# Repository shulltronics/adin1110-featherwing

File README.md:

ADIN1110 Single Pair Ethernet FeatherWing
=========================================

### By Carsten Thue-Bludworth, 2023

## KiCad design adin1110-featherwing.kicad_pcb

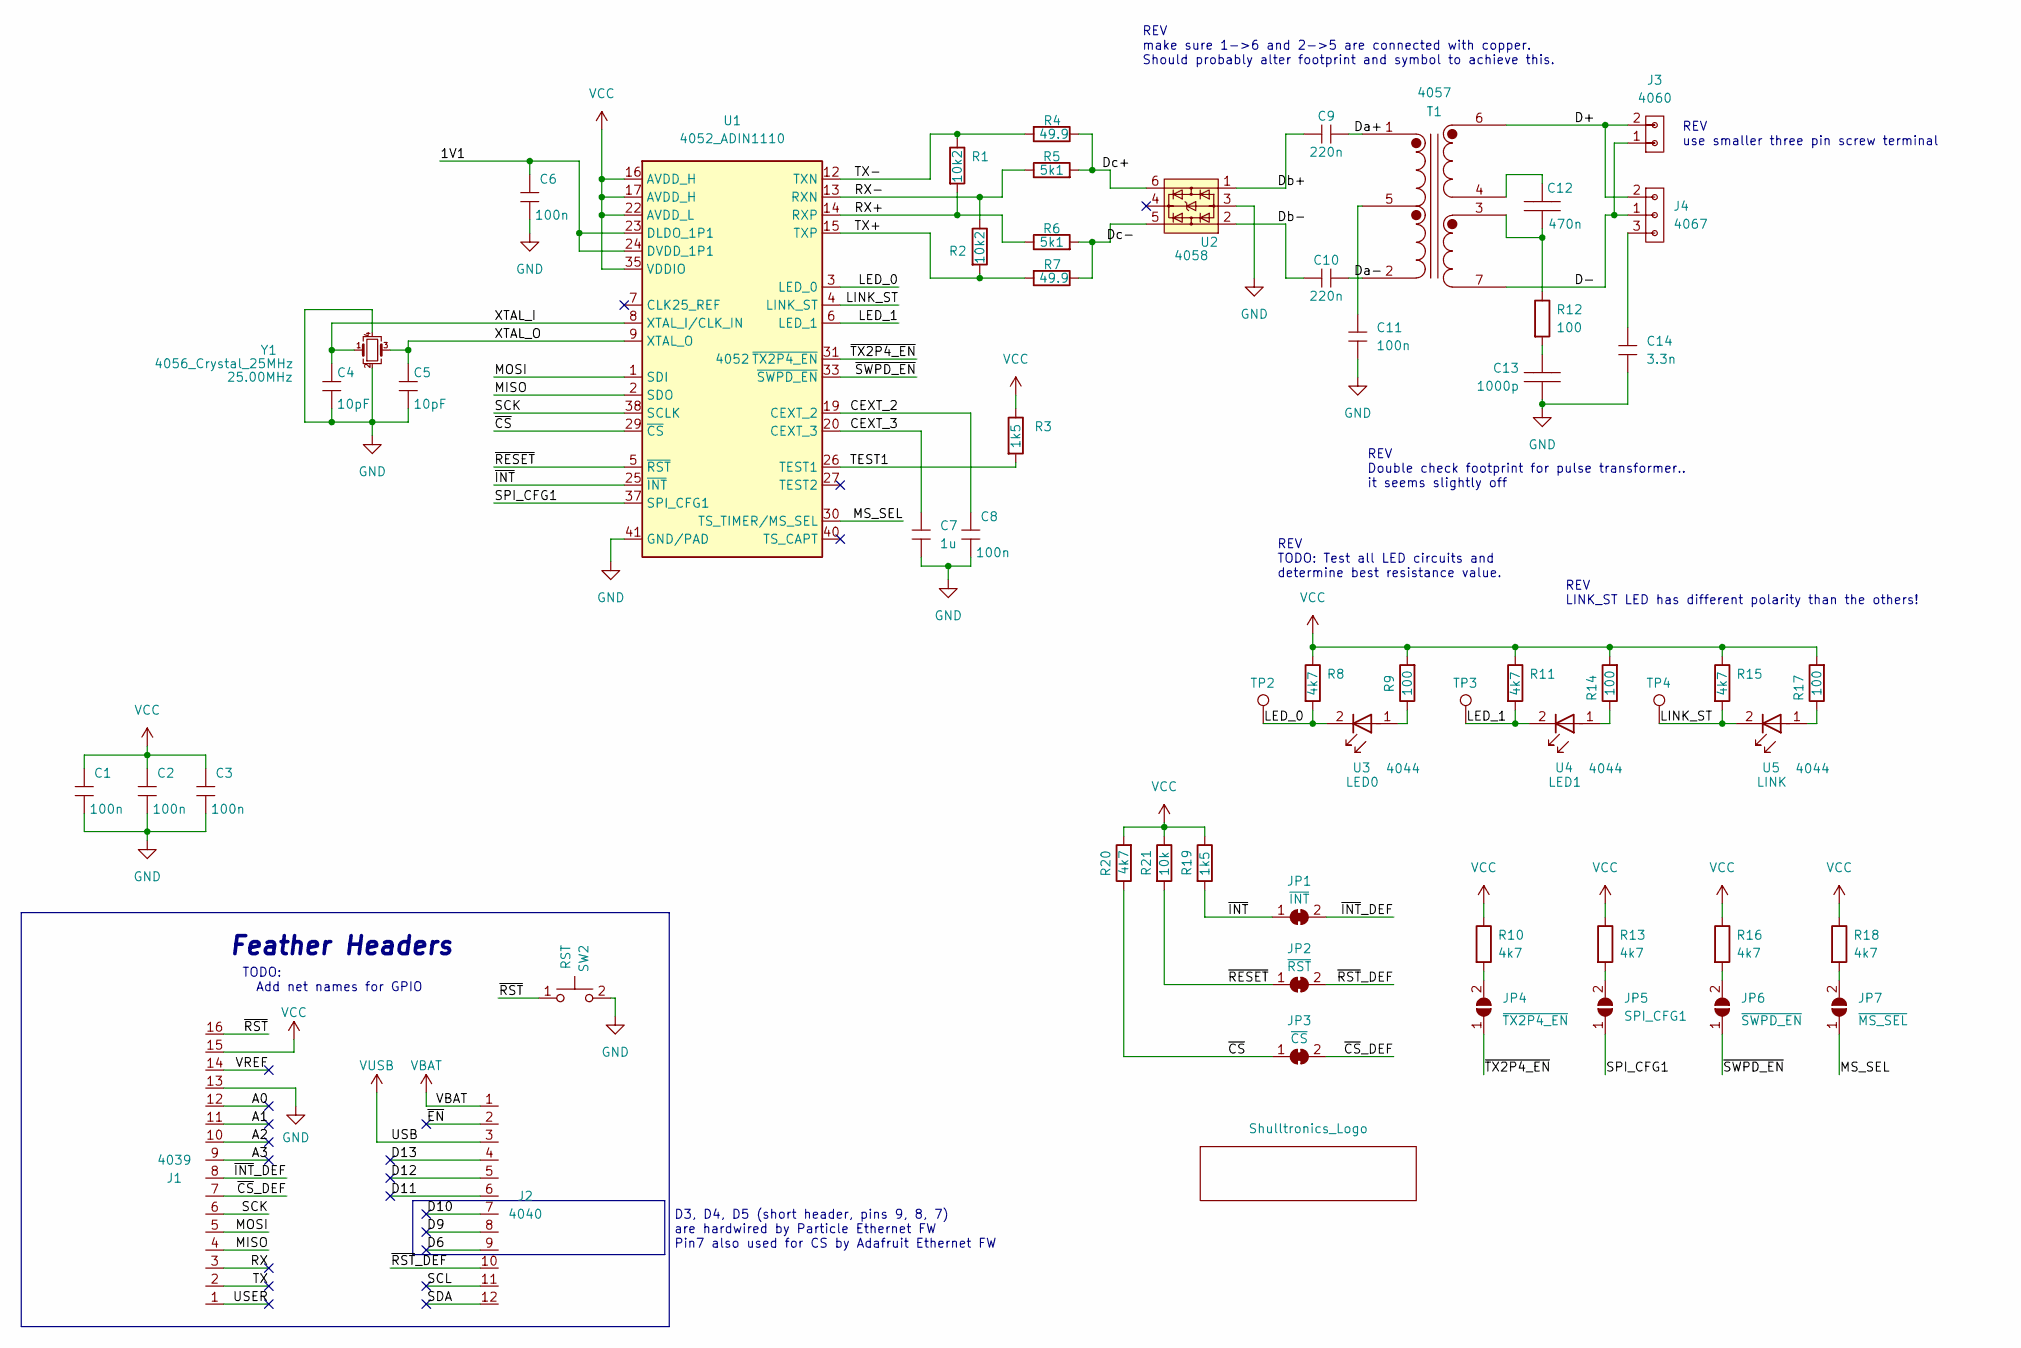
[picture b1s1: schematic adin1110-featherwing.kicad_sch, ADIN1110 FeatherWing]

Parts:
C1, C2, C3, C6, C8: 3089_Capacitor_100n_16V_0402; C_0402_HandSolder
C4, C5: 4055_Capacitor_10pF_50V_0402; C_0402_HandSolder
C7: 4013_Capacitor_1u_16V_0402; C_0402_HandSolder
C9, C10: 4059_Cap_220nF_50V_0603; R_0603_1608Metric_Pad0.98x0.95mm_HandSolder
C11: 4063_Capacitor_100n_50V_0402; C_0402_HandSolder
C12: 4061_Capacitor_470nF_100V_0805; C_0805_2012Metric_Pad1.18x1.45mm_HandSolder
C13: 4062_Capacitor_1nF_2kV_1206; C_1206_3216Metric_Pad1.33x1.80mm_HandSolder
C14: 4069_Capacitor_3.3n_50V_0402; C_0402_HandSolder
J1: 4039_Header_Male_Vert_16pin_0.1in; 4039_Header_16pos_2.54mm
J2: 4040_Header_Male_Vert_12pin_0.1in; 4040_Header_12pos_2.54mm
J3: 4060_TerminalBlock_NoScrew; TerminalBlock_bornier-2_P5.08mm
J4: 4067_SPE_IP20
JP1: ~{INT}; SolderJumper-2_P1.3mm_Bridged_Pad1.0x1.5mm
JP2: ~{RST}; SolderJumper-2_P1.3mm_Bridged_Pad1.0x1.5mm
JP3: ~{CS}; SolderJumper-2_P1.3mm_Bridged_Pad1.0x1.5mm
JP4: ~{TX2P4_EN}; SolderJumper-2_P1.3mm_Open_TrianglePad1.0x1.5mm
JP5: SPI_CFG1; SolderJumper-2_P1.3mm_Open_TrianglePad1.0x1.5mm
JP6: ~{SWPD_EN}; SolderJumper-2_P1.3mm_Open_TrianglePad1.0x1.5mm
JP7: ~{MS_SEL}; SolderJumper-2_P1.3mm_Open_TrianglePad1.0x1.5mm
L1: Shulltronics_Logo
R1, R2: 4066_Resistor_SMD_10k2_0.1W_1%_0603; R_0603_1608Metric_Pad0.98x0.95mm_HandSolder
R3, R19: 4065_Resistor_SMD_1k5_0.10W_1%; RES-0402
R4, R7: 4053_Resistor_SMD_49.9_0.125W_1%; RES-0402
R5, R6: 4009_Resistor_SMD_5k1_0.10W_1%; RES-0402
R8, R10, R11, R13, R15, R16, R18, R20: 4064_Resistor_SMD_4k7_0.10W_1%; RES-0402
R9, R12, R14, R17: 4038_Resistor_SMD_100_0.125W_1%; RES-0402
R21: 4008_Resistor_SMD_10k_0.125W_1%; RES-0402
SW2: RST; 4012_PushButton_NO_SMD
T1: 4057_Super_Tiny_Signal_Transformer
TP2: LED0; TestPoint_Pad_D2.0mm
TP3: LED1; TestPoint_Pad_D2.0mm
TP4: LINK; TestPoint_Pad_D2.0mm
U1: 4052_ADIN1110; 4052_ADIN1110_40QFN
U2: 4058_TVS_2CH_Super_Speed
U3: LED0; LED_0402
U4: LED1; LED_0402
U5: LINK; LED_0402
Y1: 4056_Crystal_25MHz; 4004-Crystal-12MHz-4Pin_2.5x2.0mm

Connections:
/1V1: C6.2, U1.23 (DLDO_1P1), U1.24 (DVDD_1P1)
/A0: J1.12
/A1: J1.11
/A2: J1.10
/A3: J1.9
/CEXT_2: C8.2, U1.19 (CEXT_2)
/CEXT_3: C7.2, U1.20 (CEXT_3)
/D6: J2.9
/D9: J2.8
/D10: J2.7
/D11: J2.6
/D12: J2.5
/D13: J2.4
/D+: J3.2, J4.2, T1.6 (OUT1A)
/D-: J3.1, J4.1, T1.7 (OUT2B)
/Da+: C9.2, T1.1 (IN+)
/Da-: C10.2, T1.2 (IN-)
/Db+: C9.1, U2.1
/Db-: C10.1, U2.2
/Dc+: R4.1, R5.2, U2.6
/Dc-: R6.2, R7.1, U2.5
/LED_0: R8.2, TP2.1, U1.3 (LED_0), U3.2 (K)
/LED_1: R11.2, TP3.1, U1.6 (LED_1), U4.2 (K)
/LINK_ST: R15.2, TP4.1, U1.4 (LINK_ST), U5.2 (K)
/MISO: J1.4, U1.2 (SDO)
/MOSI: J1.5, U1.1 (SDI)
/MS_SEL: JP7.1 (A), U1.30 (TS_TIMER/MS_SEL)
/RX: J1.3
/RX+: R1.2, R6.1, U1.14 (RXP)
/RX-: R2.1, R5.1, U1.13 (RXN)
/SCK: J1.6, U1.38 (SCLK)
/SCL: J2.11
/SDA: J2.12
/SPI_CFG1: JP5.1 (A), U1.37 (SPI_CFG1)
/TEST1: R3.2, U1.26 (TEST1)
/TX: J1.2
/TX+: R2.2, R7.2, U1.15 (TXP)
/TX-: R1.1, R4.2, U1.12 (TXN)
/USER: J1.1
/VREF: J1.14
/XTAL_I: C4.2, U1.8 (XTAL_I/CLK_IN), Y1.1
/XTAL_O: C5.2, U1.9 (XTAL_O), Y1.3
/~CS: JP3.1 (A), R20.1, U1.29 (~CS)
/~CS_DEF: J1.7, JP3.2 (B)
/~EN: J2.2
/~INT: JP1.1 (A), R19.2, U1.25 (~INT)
/~INT_DEF: J1.8, JP1.2 (B)
/~RESET: JP2.1 (A), R21.2, U1.5 (~RST)
/~RST: J1.16, SW2.1
/~RST_DEF: J2.10, JP2.2 (B)
/~SWPD_EN: JP6.1 (A), U1.33 (~SWPD_EN)
/~TX2P4_EN: JP4.1 (A), U1.31 (~TX2P4_EN)
GND: C1.1, C2.1, C3.1, C4.1, C5.1, C6.1, C7.1, C8.1, C11.1, C13.1, C14.1, J1.13, SW2.2, U1.41 (GND/PAD), U2.3, Y1.2, Y1.4
unnamed: C13.2, R12.2
unnamed: C14.2, J4.3
unnamed: JP4.2 (B), R10.2
unnamed: JP5.2 (B), R13.2
unnamed: JP6.2 (B), R16.2
unnamed: JP7.2 (B), R18.2
unnamed: C12.2, T1.4 (OUT1B)
unnamed: C12.1, R12.1, T1.3 (OUT2A)
unnamed: C11.2, T1.5 (PM)
unnamed: R9.1, U3.1 (A)
unnamed: R14.1, U4.1 (A)
unnamed: R17.1, U5.1 (A)
VBAT: J2.1
VCC: C1.2, C2.2, C3.2, J1.15, R3.1, R8.1, R9.2, R10.1, R11.1, R13.1, R14.2, R15.1, R16.1, R17.2, R18.1, R19.1, R20.2, R21.1, U1.16 (AVDD_H), U1.17 (AVDD_H), U1.22 (AVDD_L), U1.35 (VDDIO)
VUSB: J2.3

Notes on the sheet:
TODO: Add net names for GPIO
REV make sure 1->6 and 2->5 are connected with copper. Should probably alter footprint and symbol to achieve this.
Feather Headers
REV TODO: Test all LED circuits and determine best resistance value.
REV use smaller three pin screw terminal
REV Double check footprint for pulse transformer.. it seems slightly off
REV LINK_ST LED has different polarity than the others!
D3, D4, D5 (short header, pins 9, 8, 7) are hardwired by Particle Ethernet FW Pin7 also used for CS by Adafruit Ethernet FW

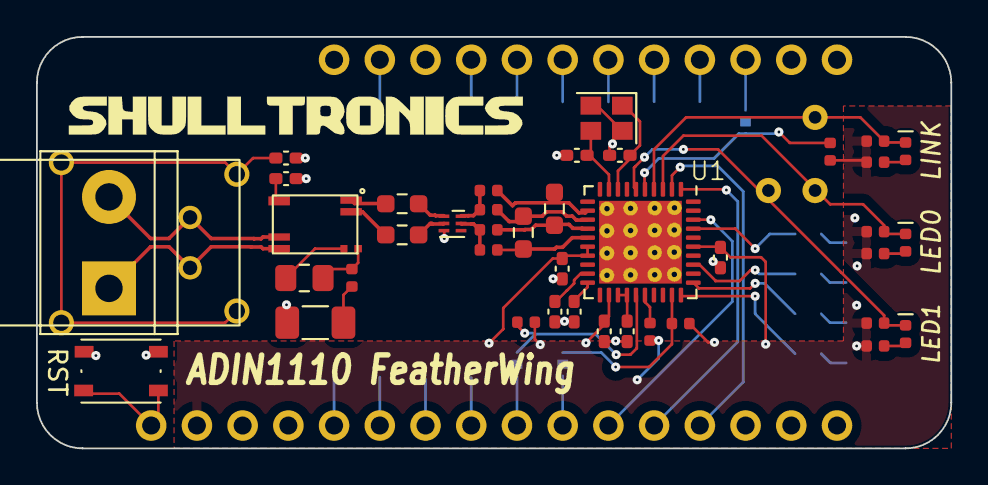
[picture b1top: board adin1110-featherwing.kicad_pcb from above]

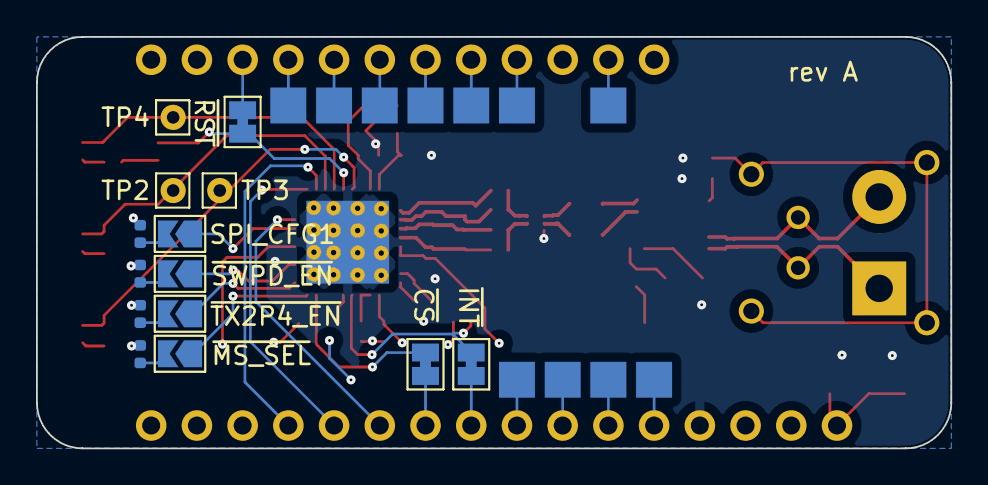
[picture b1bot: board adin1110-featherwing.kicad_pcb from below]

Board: 4 copper layers, 50.8 x 22.9 mm, 58 parts (14 on the bottom side), 49 nets.

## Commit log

2023-08-14 first commit!
2023-08-15 getting close to schematic completion
2023-08-16 sch almost done, started PCB placements
2023-08-17 ready to order
2023-08-17 added readme and image
2023-08-17 created BOM for DigiKey order
2023-08-17 as ordered for revA
2023-08-29 rev1 working with minor modification. Start taking notes for rev2 fixes
2023-08-30 more rev 2 notes
